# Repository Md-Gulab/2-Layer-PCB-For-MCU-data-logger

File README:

# 2-Layer PCB for MCU Data Logger

A 2-layer PCB designed in KiCad 10 for logging data from an MCU-based system.

## Images

### PCB Layout

### 3D View (Front)

### 3D View (Back)

### Schematic

## Overview

- **Board:** 2-layer, [width] x [height] mm
- **MCU / main ICs:** [e.g. STM32xxxx, SD card module, RTC, etc.]
- **Interfaces:** [e.g. SPI, I2C, UART, USB]
- **Power:** [e.g. 5 V via USB, 3.3 V regulator]
- **EDA tool:** KiCad 10.0

## Features

- [Feature 1]
- [Feature 2]
- [Feature 3]

## Repository Structure

```
.
├── Data_Logger/     # KiCad project (schematics, PCB layout, fp-lib-table) and Gerber files
├── Images/          # Layout, 3D renders and schematic images used in this README
├── .gitignore
└── README.md
```

## Opening the Project

1. Install [KiCad 10](https://www.kicad.org/download/).
2. Clone this repository:
   ```
   git clone https://github.com/Md-Gulab/2-Layer-PCB-For-MCU-data-logger.git
   ```
3. Open `Data_Logger/Data_Logger.kicad_pro` in KiCad.

## Manufacturing

The Gerber and drill files are exported and ready to upload to a PCB fabricator (JLCPCB, PCBWay, etc.).

| Setting | Value |
|---|---|
| Layers | 2 |
| Board thickness | 1.6 mm |
| Surface finish | [HASL / ENIG] |
| Copper weight | 1 oz |

## Author

**Md Gulab**

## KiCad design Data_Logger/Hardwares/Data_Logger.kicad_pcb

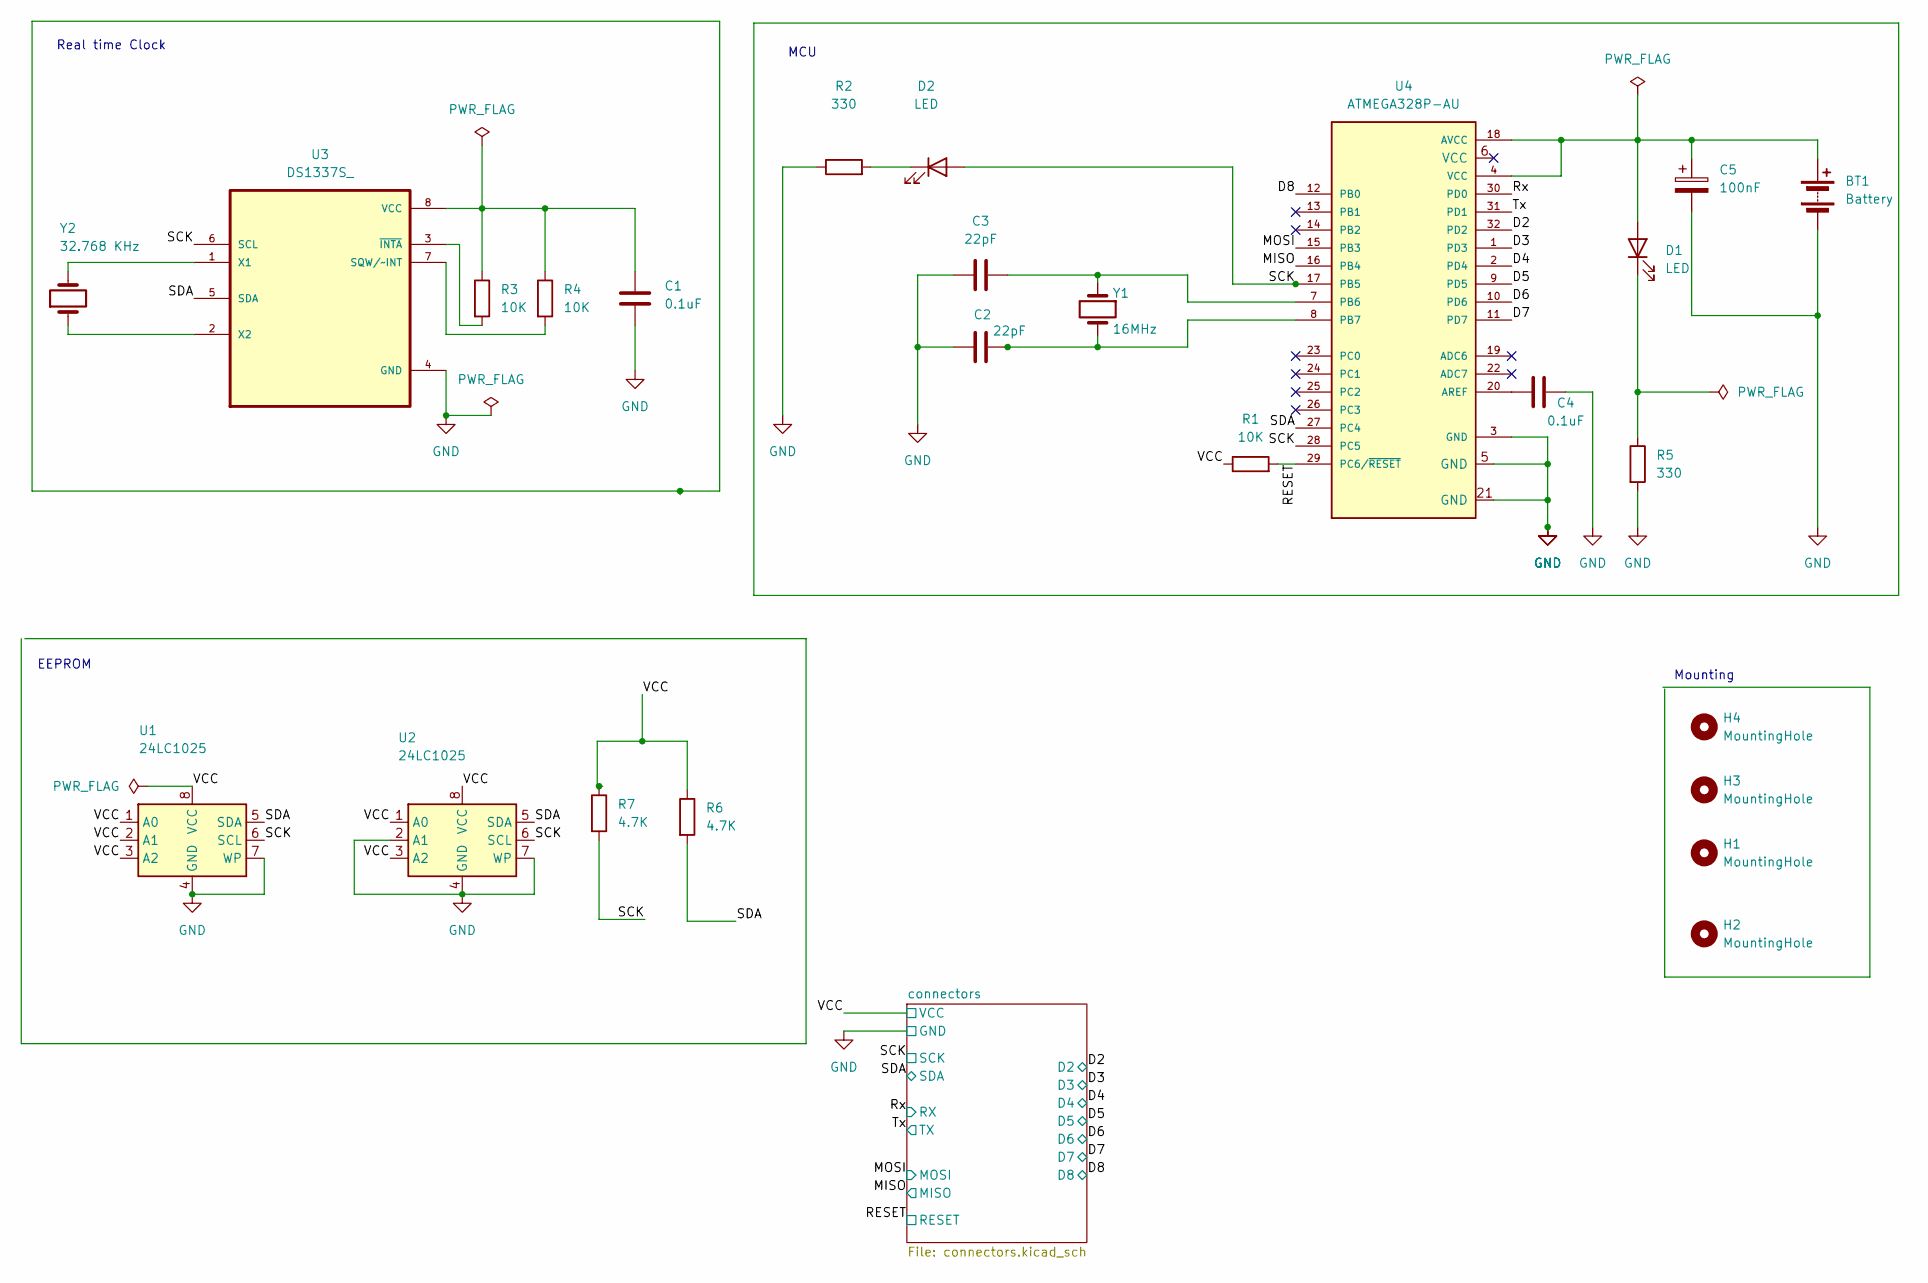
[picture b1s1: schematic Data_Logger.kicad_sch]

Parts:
BT1: Battery; PinHeader_1x02_P2.54mm_Vertical
C1, C4: 0.1uF; C_0805_2012Metric_Pad1.18x1.45mm_HandSolder
C2, C3: 22pF; C_0805_2012Metric_Pad1.18x1.45mm_HandSolder
C5: 100nF; C_0805_2012Metric_Pad1.18x1.45mm_HandSolder
D1, D2: LED; LED_0805_2012Metric
H1, H2, H3, H4: MountingHole; MountingHole_2.1mm
R1, R3, R4: 10K; R_0805_2012Metric
R2, R5: 330; R_0805_2012Metric
R6, R7: 4.7K; R_0805_2012Metric
U1, U2: 24LC1025; SOIC-8_5.3x5.3mm_P1.27mm
U3: DS1337S_; SOIC127P600X175-8N
U4: ATMEGA328P-AU; QFP80P900X900X120-32N; PARTREV 8271A
Y1: 16MHz; Crystal_SMD_5032-2Pin_5.0x3.2mm_HandSoldering
Y2: 32.768 KHz; Crystal_SMD_5032-2Pin_5.0x3.2mm_HandSoldering

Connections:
/D2: U4.32 (PD2); also elsewhere on the board
/D3: U4.1 (PD3); also elsewhere on the board
/D4: U4.2 (PD4); also elsewhere on the board
/D5: U4.9 (PD5); also elsewhere on the board
/D6: U4.10 (PD6); also elsewhere on the board
/D7: U4.11 (PD7); also elsewhere on the board
/D8: U4.12 (PB0); also elsewhere on the board
/MISO: U4.16 (PB4); also elsewhere on the board
/MOSI: U4.15 (PB3); also elsewhere on the board
/RESET: R1.2, U4.29 (PC6/~RESET); also elsewhere on the board
/Rx: U4.30 (PD0); also elsewhere on the board
/SCK: D2.2 (A), R7.2, U1.6 (SCL), U2.6 (SCL), U3.6 (SCL), U4.17 (PB5), U4.28 (PC5); also elsewhere on the board
/SDA: R6.2, U1.5 (SDA), U2.5 (SDA), U3.5 (SDA), U4.27 (PC4); also elsewhere on the board
/Tx: U4.31 (PD1); also elsewhere on the board
/VCC: R1.1, R6.1, R7.1, U1.1 (A0), U1.2 (A1), U1.3 (A2), U1.8 (VCC), U2.1 (A0), U2.3 (A2), U2.8 (VCC); also elsewhere on the board
GND: BT1.2 (-), C1.2, C2.2, C3.1, C4.2, C5.2, R2.1, R5.2, U1.4 (GND), U1.7 (WP), U2.2 (A1), U2.4 (GND), U2.7 (WP), U3.4 (GND), U4.3 (GND), U4.5 (GND), U4.21 (GND); also elsewhere on the board
unnamed: BT1.1 (+), C5.1, D1.2 (A), U4.4 (VCC), U4.18 (AVCC)
unnamed: D1.1 (K), R5.1
unnamed: D2.1 (K), R2.2
unnamed: R4.2, U3.7 (SQW/~INT)
unnamed: C1.1, R3.1, R4.1, U3.8 (VCC)
unnamed: U3.1 (X1), Y2.2
unnamed: U3.2 (X2), Y2.1
unnamed: R3.2, U3.3 (~INTA)
unnamed: C4.1, U4.20 (AREF)
unnamed: C3.2, U4.7 (PB6), Y1.1
unnamed: C2.1, U4.8 (PB7), Y1.2

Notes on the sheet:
Real time Clock
Mounting
MCU
EEPROM

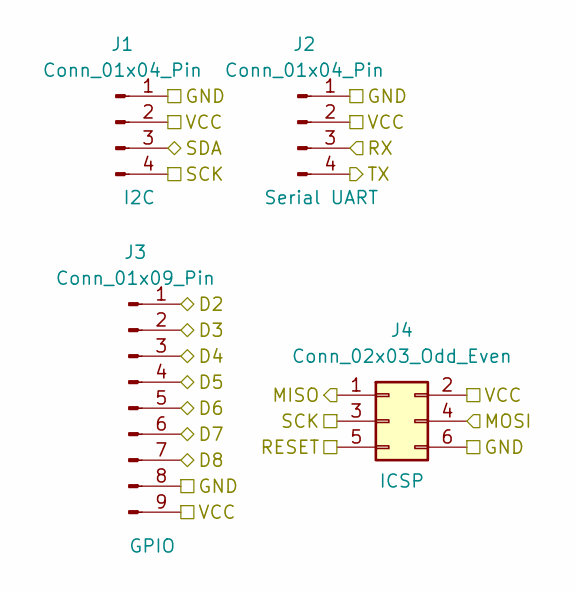
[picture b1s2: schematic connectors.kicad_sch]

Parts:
J1, J2: Conn_01x04_Pin; PinHeader_1x04_P2.54mm_Vertical
J3: Conn_01x09_Pin; PinHeader_1x09_P2.54mm_Vertical
J4: Conn_02x03_Odd_Even; PinHeader_2x03_P2.54mm_Vertical

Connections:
/D2: J3.1; also elsewhere on the board
/D3: J3.2; also elsewhere on the board
/D4: J3.3; also elsewhere on the board
/D5: J3.4; also elsewhere on the board
/D6: J3.5; also elsewhere on the board
/D7: J3.6; also elsewhere on the board
/D8: J3.7; also elsewhere on the board
/MISO: J4.1; also elsewhere on the board
/MOSI: J4.4; also elsewhere on the board
/RESET: J4.5; also elsewhere on the board
/Rx: J2.3; also elsewhere on the board
/SCK: J1.4, J4.3; also elsewhere on the board
/SDA: J1.3; also elsewhere on the board
/Tx: J2.4; also elsewhere on the board
/VCC: J1.2, J2.2, J3.9, J4.2; also elsewhere on the board
GND: J1.1, J2.1, J3.8, J4.6; also elsewhere on the board

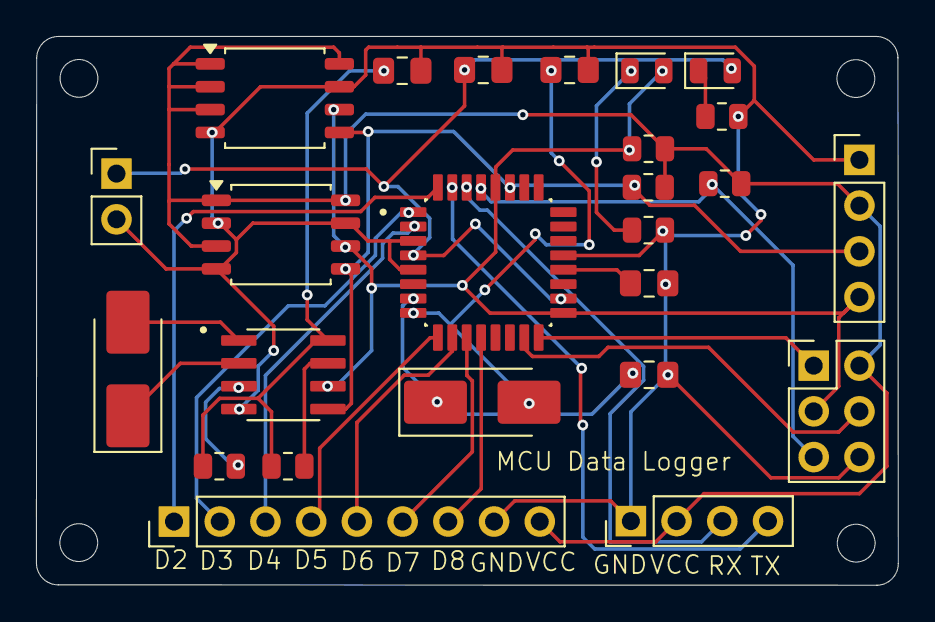
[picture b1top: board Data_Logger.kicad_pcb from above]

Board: 2 copper layers, 47.9 x 30.5 mm, 29 parts (0 on the bottom side), 27 nets.
